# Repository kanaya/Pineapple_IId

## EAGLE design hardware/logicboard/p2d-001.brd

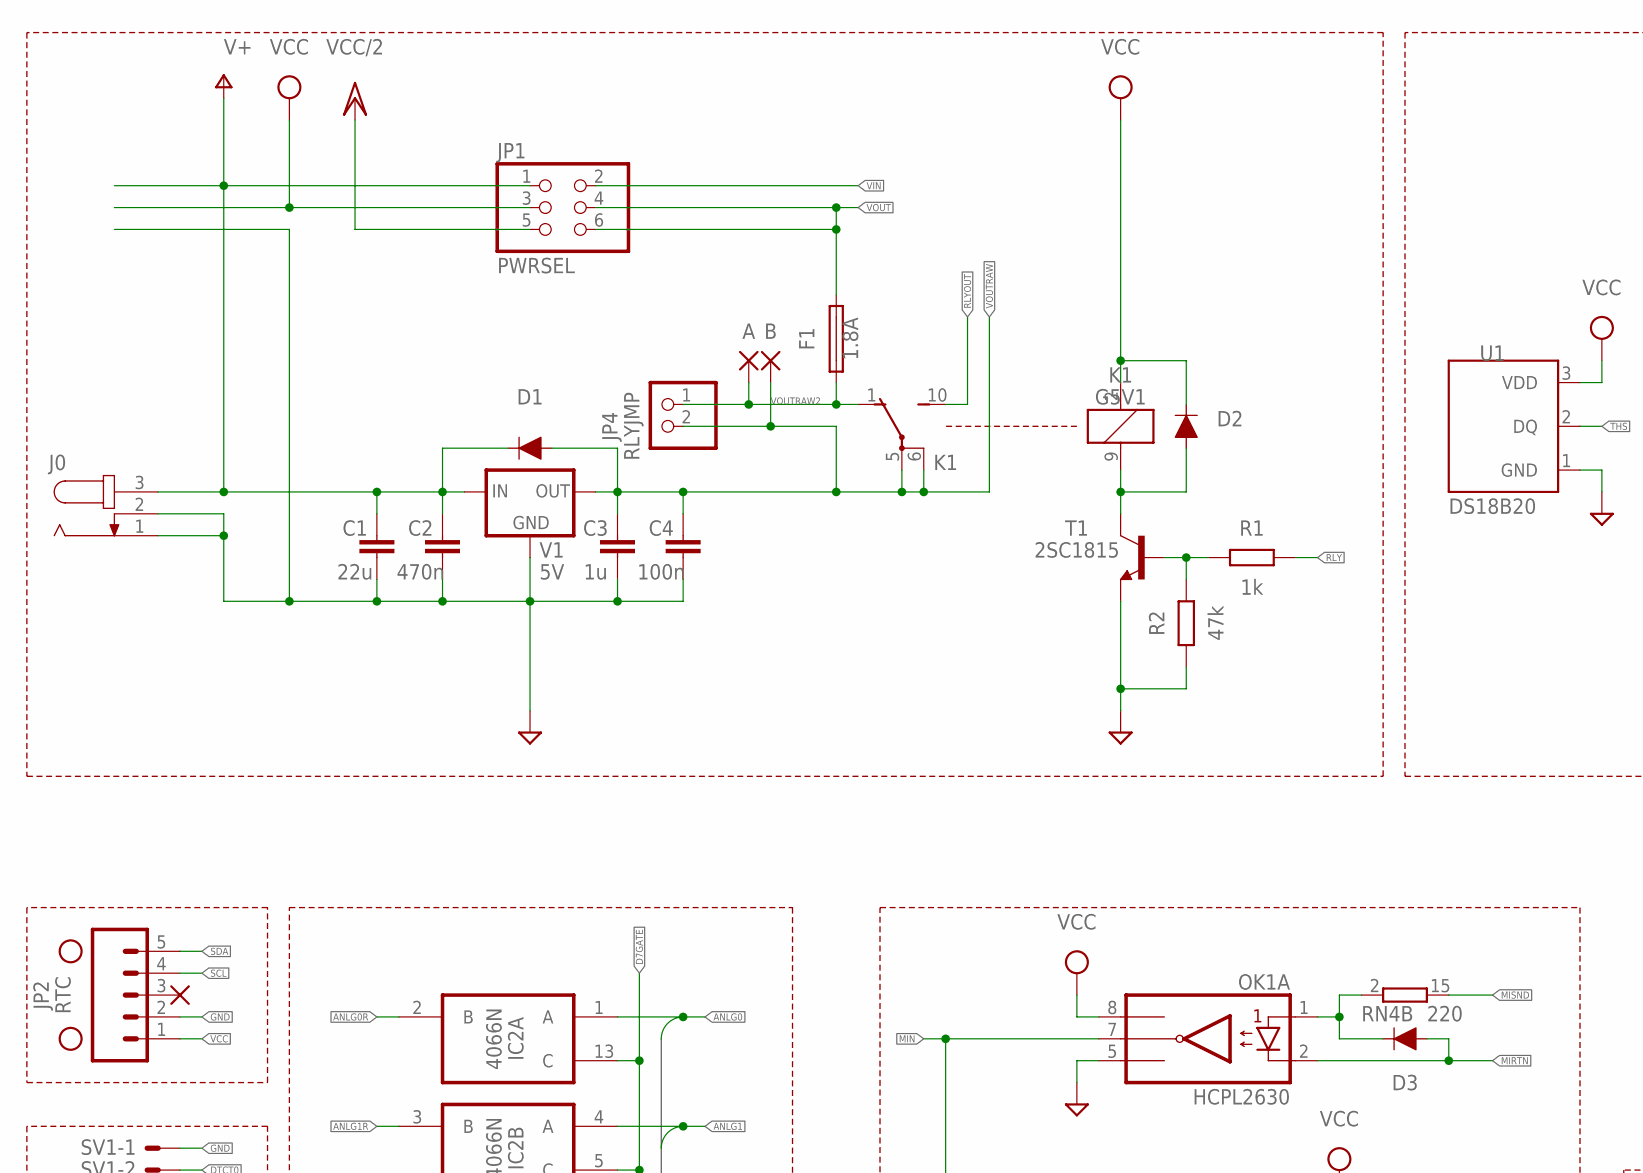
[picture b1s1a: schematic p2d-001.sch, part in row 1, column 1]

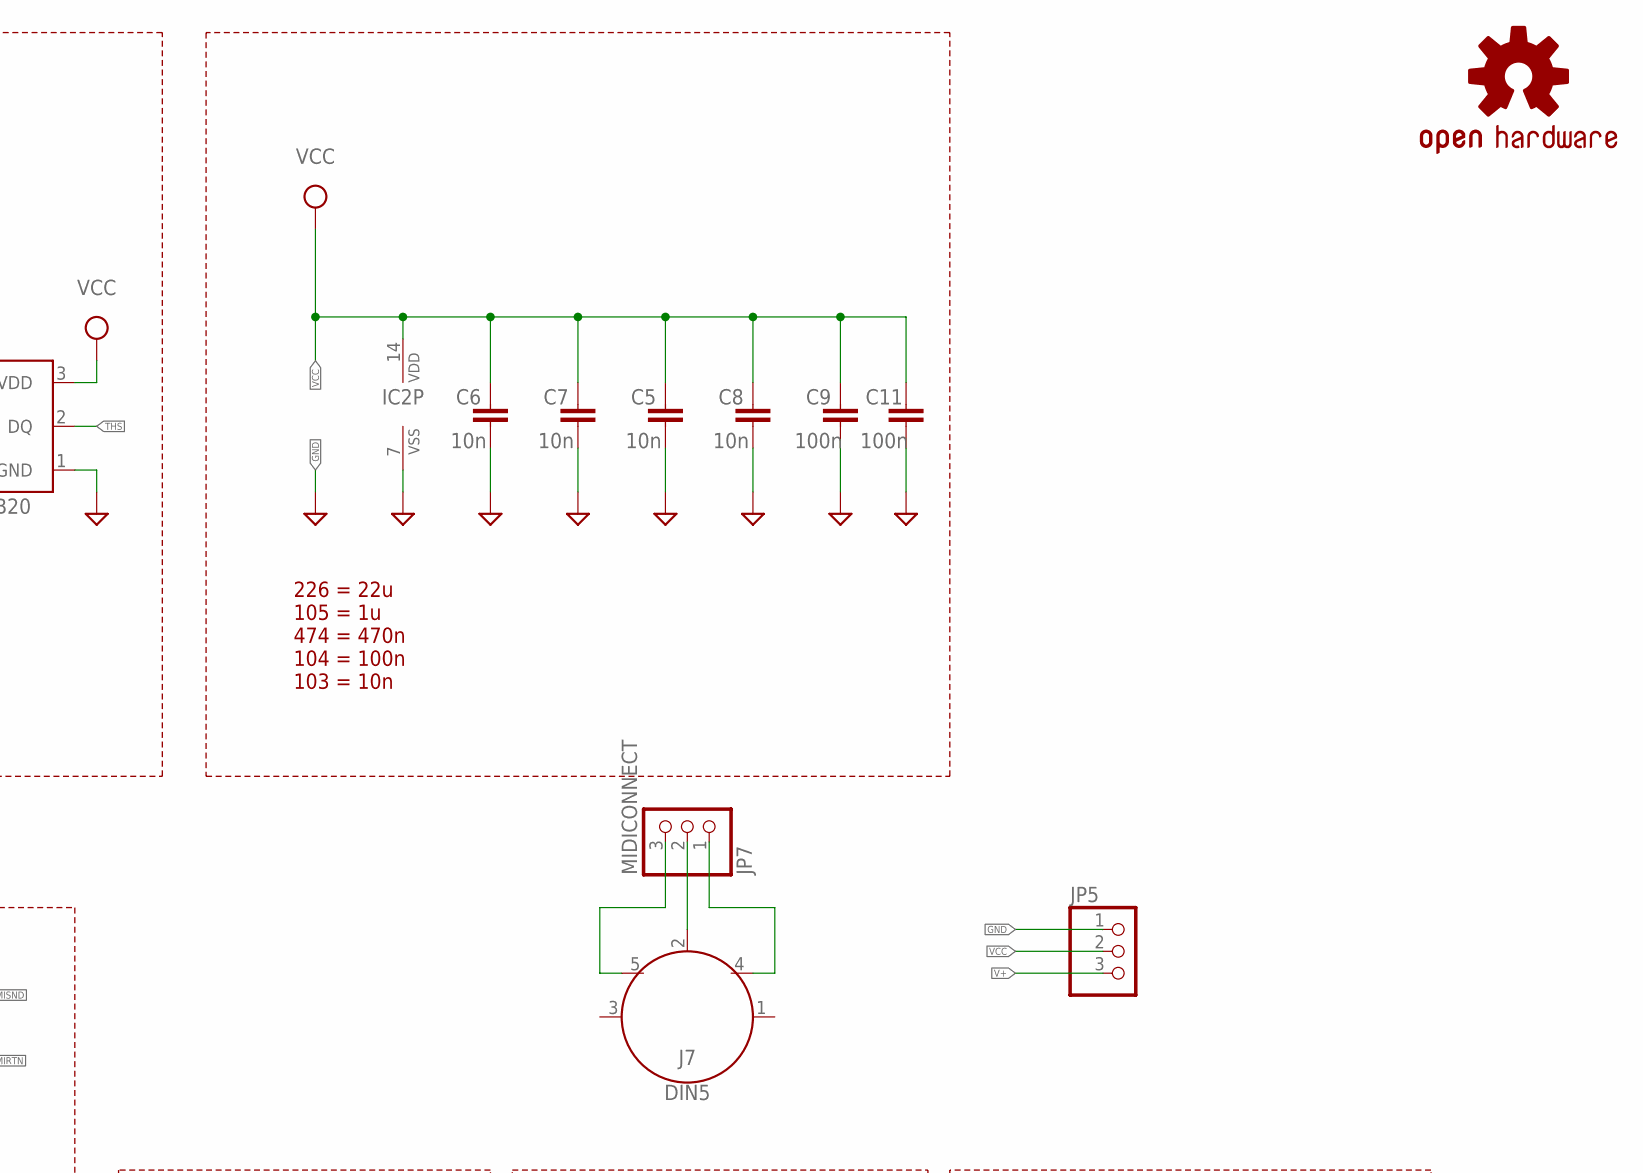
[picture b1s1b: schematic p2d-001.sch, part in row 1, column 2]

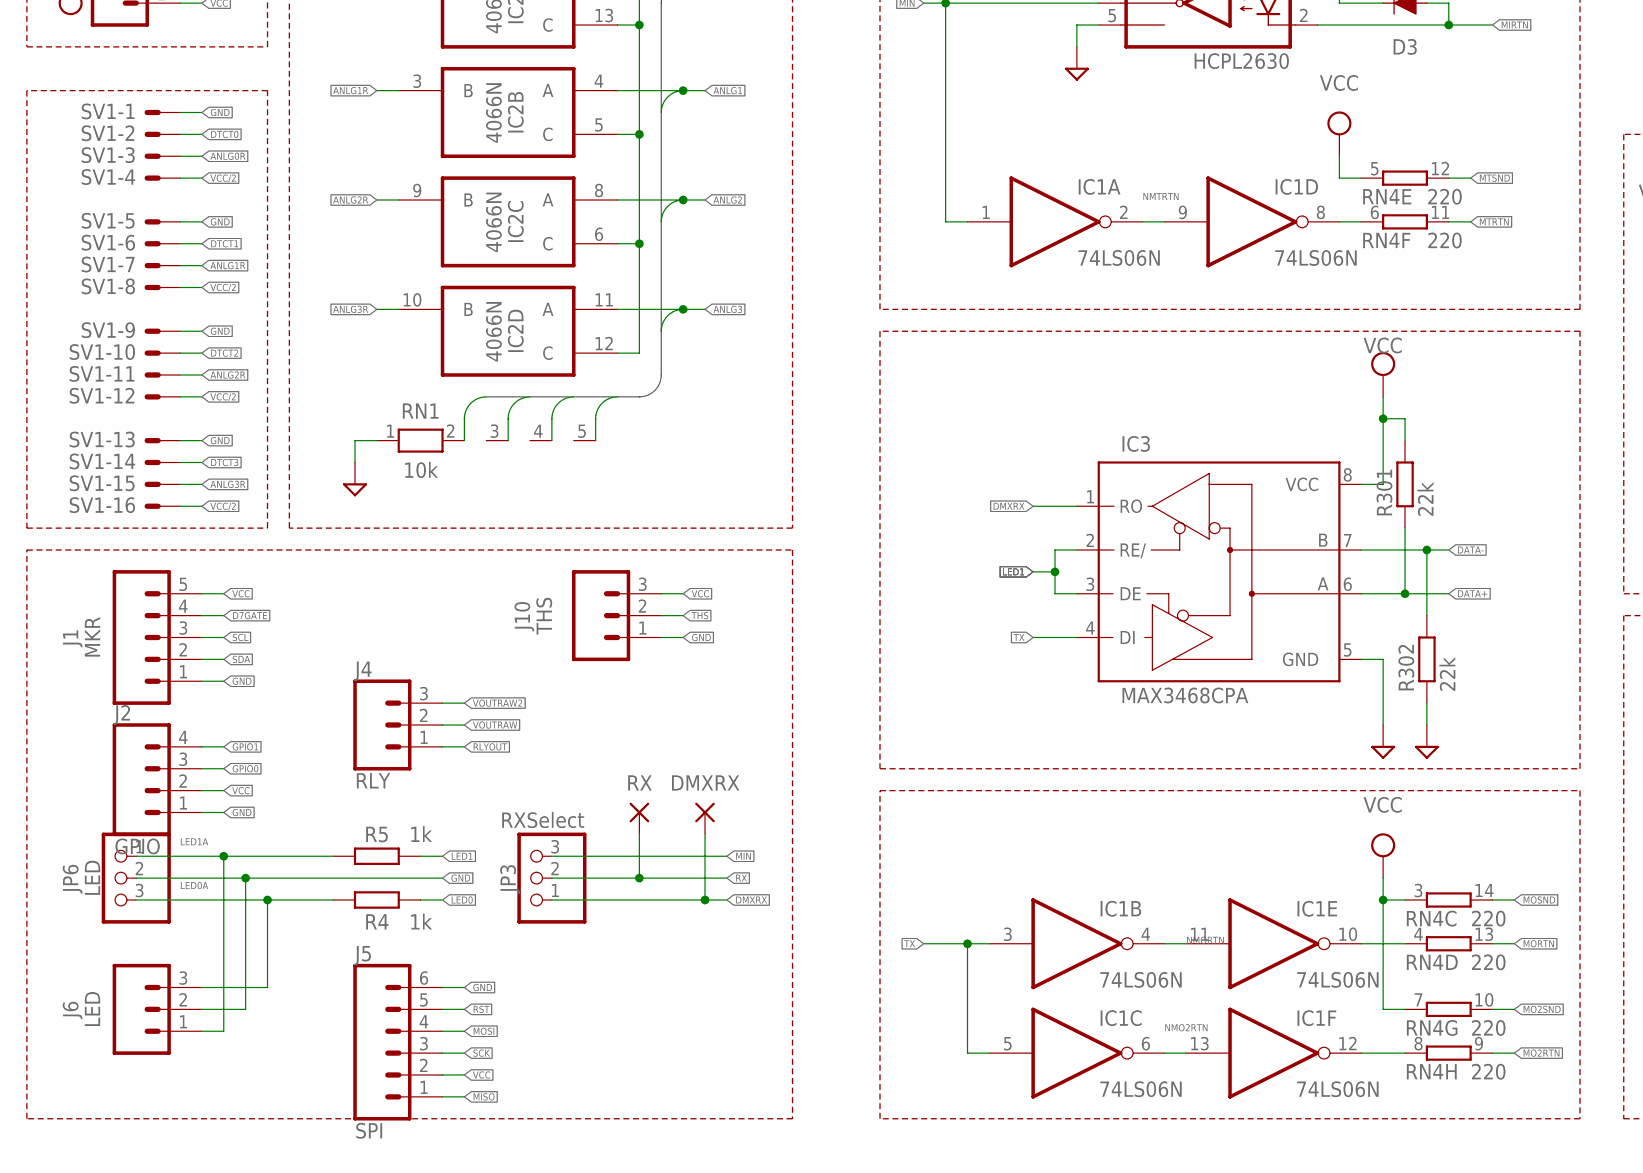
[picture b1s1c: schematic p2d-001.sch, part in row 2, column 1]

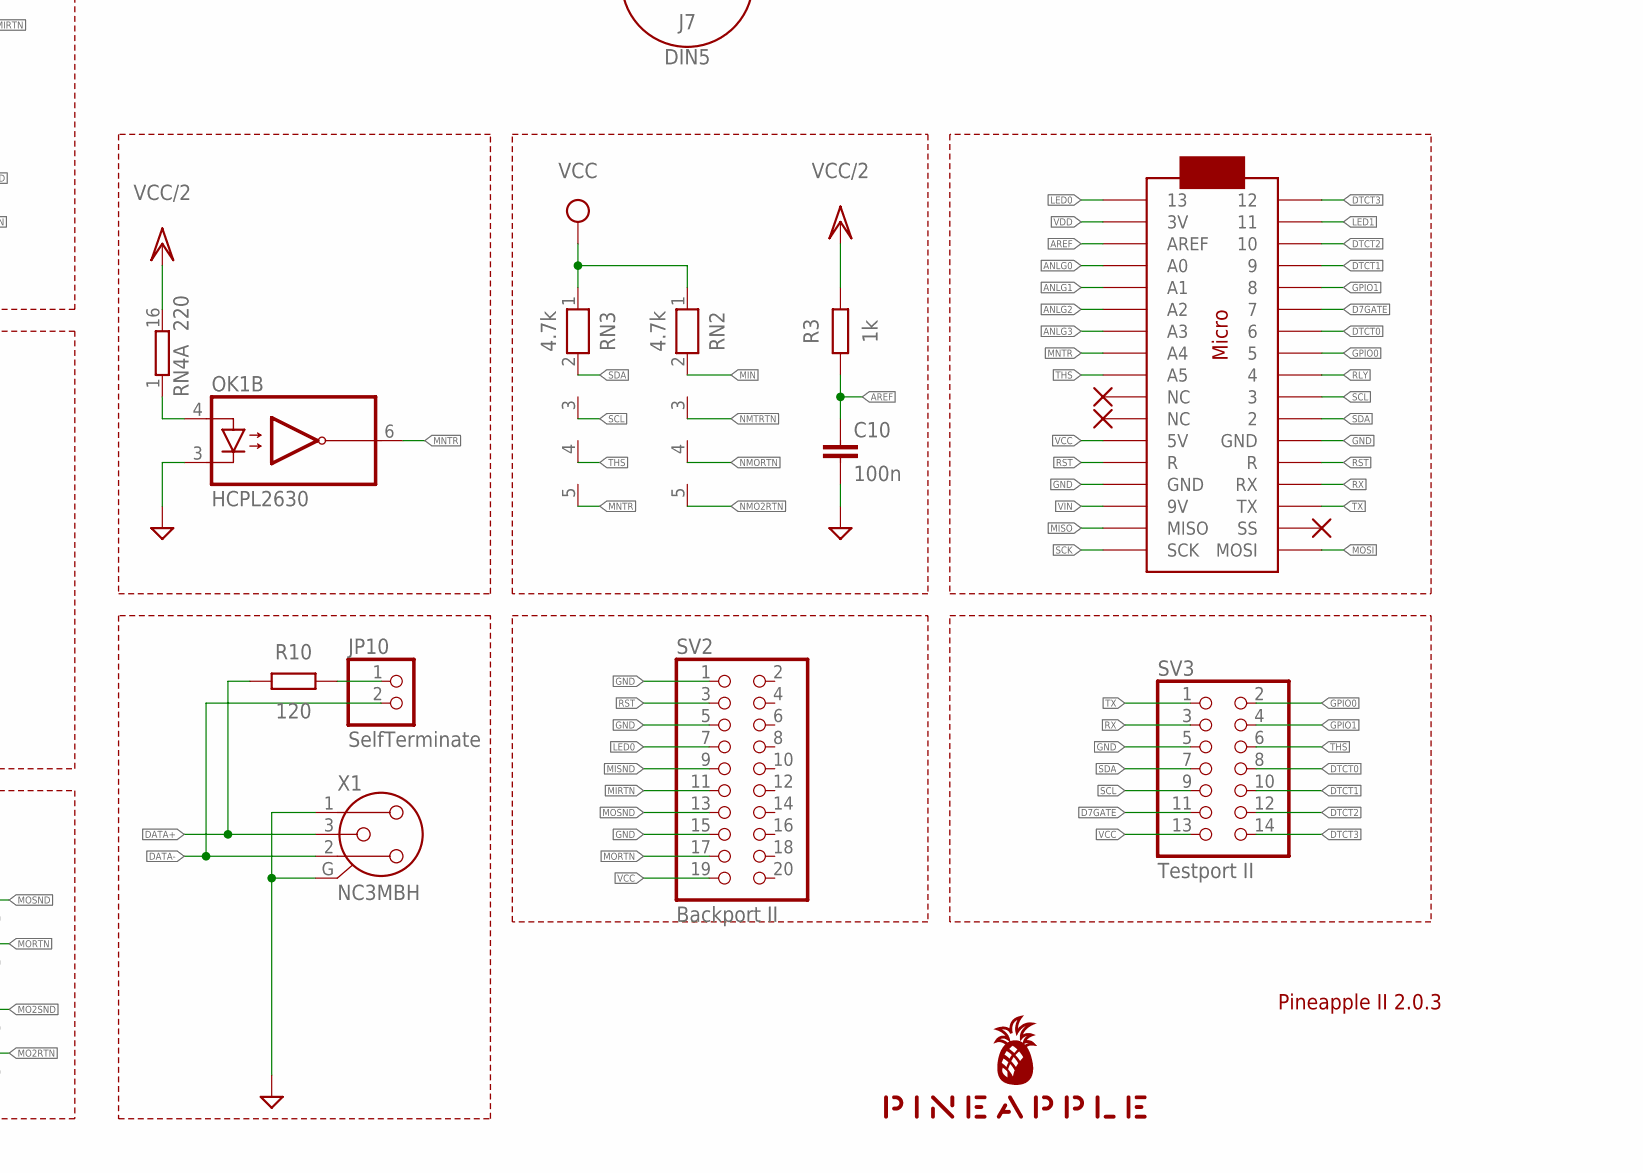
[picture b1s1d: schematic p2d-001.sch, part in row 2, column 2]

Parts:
A: SMD2; SMD1,27-2,54
B: SMD2; SMD1,27-2,54
C1: 22u; C025-050X050
C2: 470n; C050-024X044
C3: 1u; C050-024X044
C4, C9, C10, C11: 100n; C025-024X044
C5, C6, C7, C8: 10n; C025-024X044
D1, D2, D3: DIODE-1N4148
DMXRX: SMD2; SMD1,27-2,54
F1: 1.8A; TE5
H1, H2: STAND-OFF
IC1: 74LS06N; DIL14
IC2: 4066N; DIL14
IC3: MAX3468CPA; DIL08
J0: JACK-PLUG0; SPC4077
J1: MKR; JST-5-PTH
J2: GPIO; JST-4-PTH
J4: RLY; JST-3-PTH-NS
J5: SPI; 1X06_1.27MM
J6: LED; JST-3-PTH-VERT
J7: DIN5; DIN5-RA-PTH
J10: THS; JST-3-PTH
JP1: PWRSEL; 2X03
JP2: RTC; 1X05
JP3: RXSelect; 1X03
JP4: RLYJMP; 1X02
JP5: PINHD-1X3; 1X03
JP6: LED; 1X03
JP7: MIDICONNECT; 1X03
JP10: SelfTerminate; 1X02
K1: G5V1
LOGO1: OSHW-LOGOS-COPPER; OSHW-LOGO-S_COPPER
MC1: ARDUINOMICRO
OK1: HCPL2630; DIL08
R1, R3, R4, R5: 1k; 0204/5
R2: 47k; 0204/5
R10: 120; 0204/5
R301, R302: 22k; M2012
RN1: 10k; RN-5
RN2, RN3: 4.7k; RN-5
RN4: 220; DIL16
RX: SMD2; SMD1,27-2,54
SV1: ML16LE; ML16L
SV2: Backport II; 2X10
SV3: Testport II; 2X07
T1: 2SC1815; TO92-ECB
U1: DS18B20; TO-92-AMMO
U$1: PINEAPPLE450_SILK
V1: 5V; 78XXL
X1: NC3MBH

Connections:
ANLG0: IC2.1 (A), MC1.P$31 (A0), RN1.2
ANLG0R: IC2.2 (B), SV1.3
ANLG1: IC2.4 (A), MC1.P$30 (A1), RN1.3
ANLG1R: IC2.3 (B), SV1.7
ANLG2: IC2.8 (A), MC1.P$29 (A2), RN1.4
ANLG2R: IC2.9 (B), SV1.11
ANLG3: IC2.11 (A), MC1.P$28 (A3), RN1.5
ANLG3R: IC2.10 (B), SV1.15
AREF: C10.1, MC1.P$32 (AREF), R3.1
D7GATE: IC2.5 (C), IC2.6 (C), IC2.12 (C), IC2.13 (C), J1.4, MC1.P$6 (7), SV3.11
DATA+: IC3.6 (A), R10.1, R301.1, X1.3
DATA+R: JP10.1, R10.2
DATA-: IC3.7 (B), JP10.2, R302.2, X1.2
DIN2: J7.2, JP7.2
DIN4: J7.4, JP7.1
DIN5: J7.5, JP7.3
DMXRX: DMXRX.1, IC3.1 (RO), JP3.1
DTCT0: MC1.P$7 (6), SV1.2, SV3.8
DTCT1: MC1.P$4 (9), SV1.6, SV3.10
DTCT2: MC1.P$3 (10), SV1.10, SV3.12
DTCT3: MC1.P$1 (12), SV1.14, SV3.14
GND: C1.2, C2.2, C3.2, C4.2, C5.2, C6.2, C7.2, C8.2, C9.2, C10.2, C11.2, IC1.7 (GND), IC2.7 (VSS), IC3.5 (GND), J0.1, J0.2, J1.1, J2.1, J5.6, J6.2, J10.1, JP2.2, JP5.1, JP6.2, MC1.P$12 (GND), MC1.P$21 (GND), OK1.3 (C2), OK1.5 (GND), R2.1, R302.1, RN1.1, SV1.1, SV1.5, SV1.9, SV1.13, SV2.1, SV2.5, SV2.15, SV3.5, T1.E, U1.1 (GND), V1.GND, X1.1, X1.G
GPIO0: J2.3, MC1.P$8 (5), SV3.2
GPIO1: J2.4, MC1.P$5 (8), SV3.4
LED0: MC1.P$34 (13), R4.2, SV2.7
LED0A: J6.3, JP6.3, R4.1
LED1: IC3.2 (RE/), IC3.3 (DE), MC1.P$2 (11), R5.2
LED1A: J6.1, JP6.1, R5.1
MIN: IC1.1 (I), JP3.3, OK1.7 (VO1), RN2.2
MIRTN: D3.A, OK1.2 (C1), SV2.11
MISND: RN4.15 (2), SV2.9
MISNDA: D3.C, OK1.1 (A1), RN4.2 (1)
MISO: J5.1, MC1.P$19 (MISO)
MNTR: MC1.P$27 (A4), OK1.6 (VO2), RN3.5
MNTRA: OK1.4 (A2), RN4.1
MO2RTN: RN4.9 (2)
MO2RTNR: IC1.12 (O), RN4.8 (1)
MO2SND: RN4.10 (2)
MORTN: RN4.13 (2), SV2.17
MORTNR: IC1.10 (O), RN4.4 (1)
MOSI: J5.4, MC1.P$17 (MOSI)
MOSND: RN4.14 (2), SV2.13
MTRTN: RN4.11 (2)
MTRTNR: IC1.8 (O), RN4.6 (1)
MTSND: RN4.12 (2)
NMO2RTN: IC1.6 (O), IC1.13 (I), RN2.5
NMORTN: IC1.4 (O), IC1.11 (I), RN2.4
NMTRTN: IC1.2 (O), IC1.9 (I), RN2.3
RLY: MC1.P$9 (4), R1.2
RLYDRV: R1.1, R2.2, T1.B
RLYOUT: J4.1, K1.10 (S)
RLYSNK: D2.A, K1.9 (2), T1.C
RST: J5.5, MC1.P$13 (R), MC1.P$22 (R), SV2.3
RX: JP3.2, MC1.P$14 (RX), RX.1, SV3.3
SCK: J5.3, MC1.P$18 (SCK)
SCL: J1.3, JP2.4, MC1.P$10 (3), RN3.3, SV3.9
SDA: J1.2, JP2.5, MC1.P$11 (2), RN3.2, SV3.7
THS: J10.2, MC1.P$26 (A5), RN3.4, SV3.6, U1.2 (DQ)
TX: IC1.3 (I), IC1.5 (I), IC3.4 (DI), MC1.P$15 (TX), SV3.1
V+: C1.1, C2.1, D1.C, J0.3, JP1.1, JP5.3, V1.IN
VCC: C5.1, C6.1, C7.1, C8.1, C9.1, C11.1, D2.C, IC1.14 (VCC), IC2.14 (VDD), IC3.8 (VCC), J1.5, J2.2, J5.2, J10.3, JP1.3, JP2.1, JP5.2, K1.2 (1), MC1.P$23 (5V), OK1.8 (VCC), R301.2, RN2.1, RN3.1, RN4.3 (1), RN4.5 (1), RN4.7 (1), SV2.19, SV3.13, U1.3 (VDD)
VCC/2: JP1.5, R3.2, RN4.16 (2), SV1.4, SV1.8, SV1.12, SV1.16
VDD: MC1.P$33 (3V)
VIN: JP1.2, MC1.P$20 (9V)
VOUT: F1.2, JP1.4, JP1.6
VOUTRAW: B.1, C3.1, C4.1, D1.A, J4.2, JP4.2, K1.5, K1.6, V1.OUT
VOUTRAW2: A.1, F1.1, J4.3, JP4.1, K1.1 (O)

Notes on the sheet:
Pineapple II 2.0.3
226 = 22u 105 = 1u 474 = 470n 104 = 100n 103 = 10n

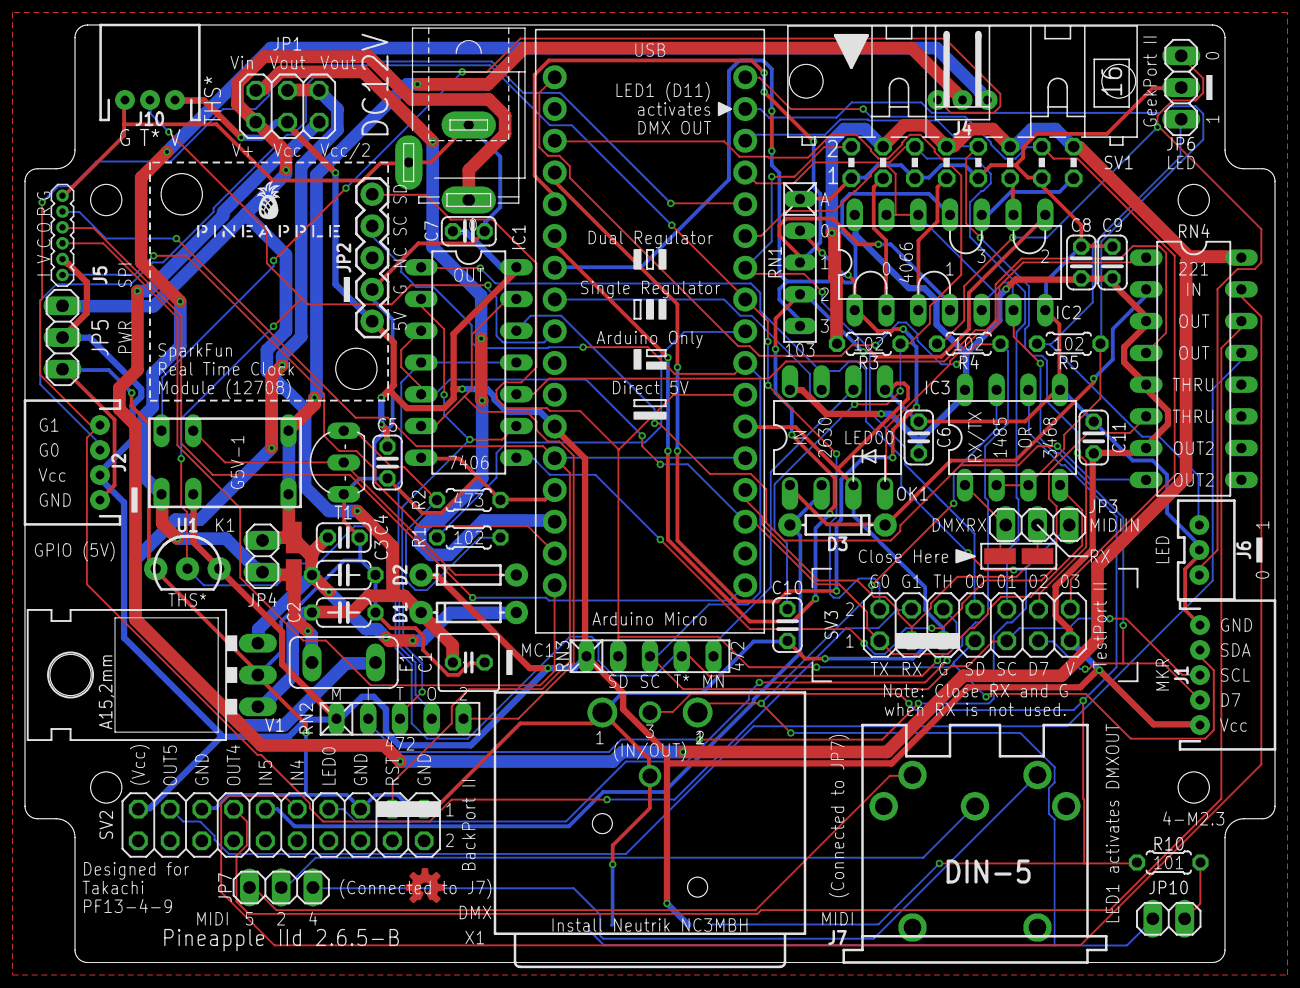
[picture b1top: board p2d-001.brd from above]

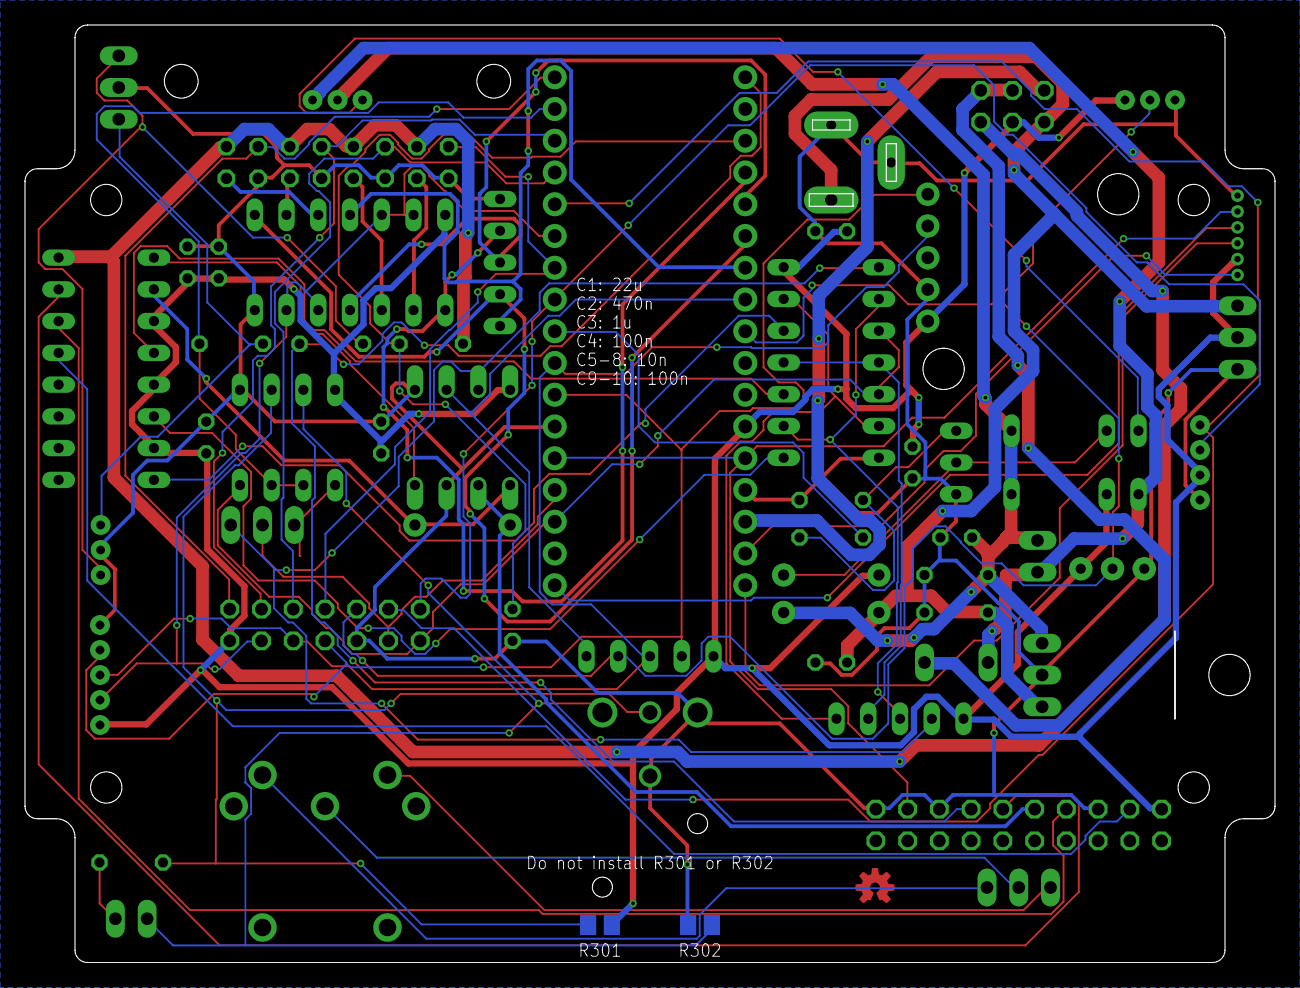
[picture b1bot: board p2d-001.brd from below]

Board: 2 copper layers, 100.0 x 75.0 mm, 64 parts (2 on the bottom side), 62 nets.

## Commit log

2021-12-10 Imported from Pineapple IIb 2.5.0-RC.
2021-12-11 Changed dimension of the board.
2021-12-12 Put all parts on board.
2021-12-12 Design of transceiver.
2021-12-13 Get MIDI back.
2021-12-13 Try. Error.
2021-12-17 Routing test.
2021-12-17 First try.
2021-12-18 Looks ok.
2021-12-19 Fixed silk and wiring.
2021-12-29 Fixed silk.
2021-12-29 Moved GeekPort right by 1mm.
2021-12-29 GND pattern.
2021-12-29 Added J10 for external thermal sensor.
2021-12-29 Added C11.
2021-12-30 New TestPort II.
2021-12-30 Added pull-up R to DMX signals.
2021-12-31 Cleaning up.
2021-12-31 Clean up.
2021-12-31 Silk.
2022-01-02 Now DMX's Data- has pull-down R., not pull-up.
2022-01-03 Changed DMX pull-up/down resisters to surface mount.
2022-01-18 Added restricted zone, added J11 for panel-mount XLR con.
2022-01-18 Renamed J11 to XLR.
2022-01-18 Added silk pattern.
2022-01-19 Changed size of logic board to fit in the case.
2022-01-19 Change size of the logic board.
2022-01-20 Changed silk of JP10.
2022-01-26 Changed dimension of the logic board to fit the base panel.
2022-01-26 Changed corner radiuses.
2022-01-26 Fixed restricted zones.
2022-01-26 Removed power pads.
2022-01-26 Routed (finally).
2022-01-29 Changed arrangement of R net.
2022-01-31 Now supports MIDI IN/OUT.
2022-02-02 Fixed corner radium of right-bottom.
2022-02-02 Added restricted zones.
2022-02-11 Changed silk of R4 and R5.
2022-06-02 Changed version number to 0.0.3-B.
2022-06-08 Updated silk.
2022-06-08 Silk and signal names.
2022-06-08 Update silk.
2022-08-03 Fixed connector value.
2022-08-16 Half-pitch SPI. 4p GPIO.
2022-08-16 Fixed GPIO. Removed JP5.
2022-08-23 Silk (DC9V -> DC12V).
2022-08-24 Removed silk of J4.
2022-08-29 SPI and PWR port.
2022-09-17 J5 and J20.

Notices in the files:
parts and their libraries:
SparkFun-DiscreteSemi: Licensing: Creative Commons ShareAlike 4.0 International - https://creativecommons.org/licenses/by-sa/4.0
